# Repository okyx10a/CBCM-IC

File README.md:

# CBCM-IC Testing Platform
**Full-stack mixed-signal test fixture for Charge-Based Capacitance Measurement ICs**  
Designed, fabricated, and validated at York University (2018–2019)

*4-layer mixed-signal test board with separated analog/digital ground planes*

## Directory Structure
├── Hardware/                       → Altium project  
├── Software/                       → Arduino code + PyQt GUI  
├── Photos/                         → Assembly  
├── Test results/                   → Raw data and measurement data  
├── CBCM project summery.docx       → Test fixture construction explanation  
├── Tools chain setup.txt           → Note for succeeding developer  
└── README.md

## Key Features
- 4-layer KiCad design with proper analog/digital ground splitting
- SAM3X8E ARM Cortex-M3 (Arduino Due core) for real-time pattern generation and data acquisition
- Interfaces: SPI (20 MHz), UART
- SMT soldering down to 0603 passives and QFN packages (hand-soldered prototype)
- Automated measurement and data logging via Python + PyQt GUI

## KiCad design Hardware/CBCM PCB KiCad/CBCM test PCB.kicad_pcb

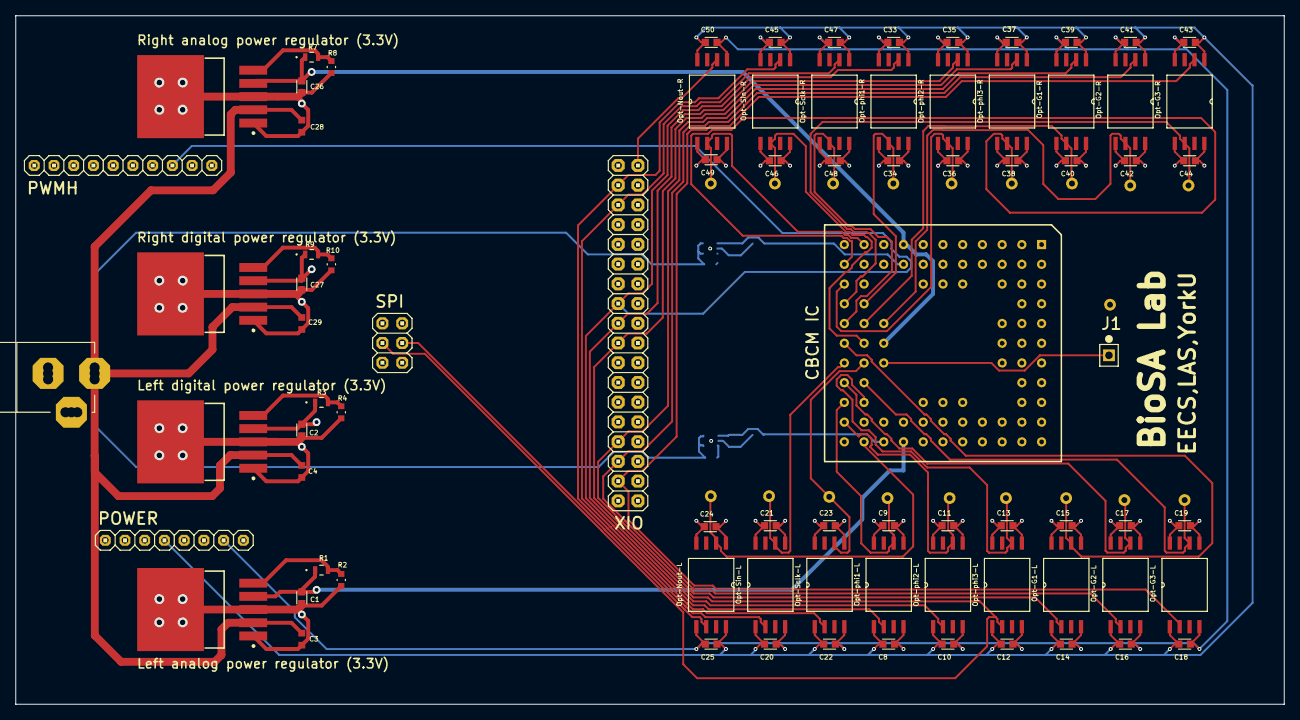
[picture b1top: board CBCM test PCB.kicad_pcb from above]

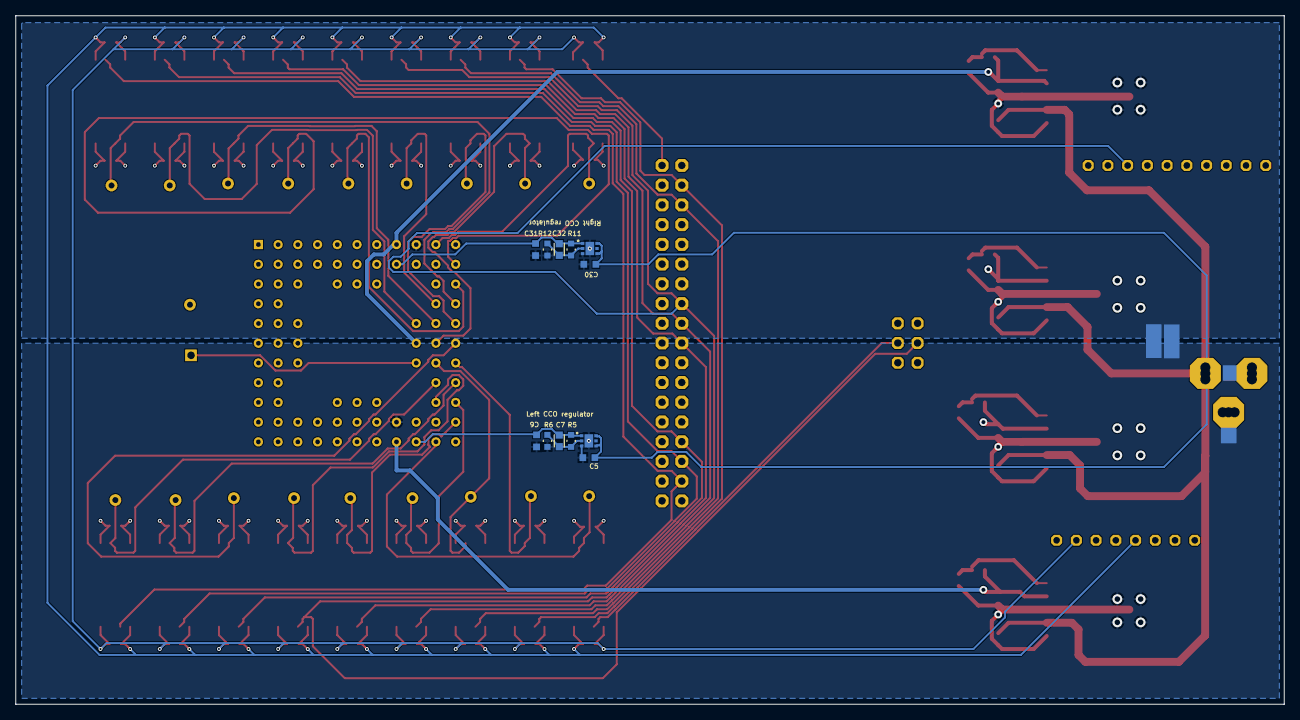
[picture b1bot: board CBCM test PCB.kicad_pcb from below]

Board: 4 copper layers, 163.3 x 88.6 mm, 99 parts (22 on the bottom side), 49 nets.

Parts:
C1, C2, C7, C8, C9, C10, C11, C12, C13, C14, C15, C16, C17, C18, C19, C20, C21, C22, C23, C24, C25, C26, C27, C32, C33, C34, C35, C36, C37, C38, C39, C40, C41, C42, C43, C44, C45, C46, C47, C48, C49, C50: C; CAPC1608X9N
C3, C4, C5, C6, C28, C29, C30, C31: C; CAP_GRM_188
CBCM IC: CBCM IC; PGA85x11
J1: 87224-1
Left CCO regulator: NCP705MTADJTCG; WDFN6
Left analog power regulator (3.3V): TPS75901KTTR; TO-263-5
Left digital power regulator (3.3V): TPS75901KTTR; TO-263-5
Opt-G1-L, Opt-G1-R, Opt-G2-L, Opt-G2-R, Opt-G3-L, Opt-G3-R: ADUM210N1BRIZ; SOIC127P1150X330-8N
Opt-Nout-L: ADUM210N1BRIZ; SOIC127P1150X330-8N
Opt-Nout-R: ADUM210N1BRIZ; SOIC127P1150X330-8N
Opt-Sclk-L: ADUM210N1BRIZ; SOIC127P1150X330-8N
Opt-Sclk-R: ADUM210N1BRIZ; SOIC127P1150X330-8N
Opt-Sin-L: ADUM210N1BRIZ; SOIC127P1150X330-8N
Opt-Sin-R: ADUM210N1BRIZ; SOIC127P1150X330-8N
Opt-phi1-L, Opt-phi1-R, Opt-phi2-L, Opt-phi2-R, Opt-phi3-L, Opt-phi3-R: ADUM210N1BRIZ; SOIC127P1150X330-8N
POWER: 8x1F-H8.5; 1X08
PWMH: 10x1F-H8.5; 1X10
R1, R3, R7, R9: R; RES_0816
R2, R4, R5, R6, R8, R10, R11, R12: R; RC0603N
Right CCO regulator: NCP705MTADJTCG; WDFN6
Right analog power regulator (3.3V): TPS75901KTTR; TO-263-5
Right digital power regulator (3.3V): TPS75901KTTR; TO-263-5
SPI: 3x2M; 2X03
X2: *; POWERSUPPLY_DC-21MM
XIO: 18x2F-H8.5; 2X18
tie1, tie2, tie3, tie4, tie5, tie6: Net Tie; net_tie

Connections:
+5: C3.2, C4.2, C5.2, C28.2, C29.2, C30.2, Left CCO regulator.4, Left CCO regulator.6, Left analog power regulator (3.3V).2, Left digital power regulator (3.3V).2, Right CCO regulator.4, Right CCO regulator.6, Right analog power regulator (3.3V).2, Right digital power regulator (3.3V).2, X2.2, X2.8, X2.9
D_GND: C2.1, C4.1, C9.2, C11.2, C13.2, C15.2, C17.2, C19.2, C21.2, C23.2, C24.2, C27.1, C29.1, C34.2, C36.2, C38.2, C40.2, C42.2, C44.2, C46.2, C48.2, C49.2, CBCM IC.K10, Left digital power regulator (3.3V).1, Left digital power regulator (3.3V).3, Left digital power regulator (3.3V).6, Opt-G1-L.5, Opt-G1-R.5, Opt-G2-L.5, Opt-G2-R.5, Opt-G3-L.5, Opt-G3-R.5, Opt-Nout-L.4, Opt-Nout-R.4, Opt-Sclk-L.5, Opt-Sclk-R.5, Opt-Sin-L.5, Opt-Sin-R.5, Opt-phi1-L.5, Opt-phi1-R.5, Opt-phi2-L.5, Opt-phi2-R.5, Opt-phi3-L.5, Opt-phi3-R.5, R4.2, R10.2, Right digital power regulator (3.3V).1, Right digital power regulator (3.3V).3, Right digital power regulator (3.3V).6, tie3.0, tie6.0
G1: Opt-G1-L.2, Opt-G1-R.2, XIO.29
G1-L: CBCM IC.L6, Opt-G1-L.6
G1-R: CBCM IC.K5, Opt-G1-R.6
G2: Opt-G2-L.2, Opt-G2-R.2, XIO.31
G2-L: CBCM IC.L8, Opt-G2-L.6
G2-R: CBCM IC.J5, Opt-G2-R.6
G3: Opt-G3-L.2, Opt-G3-R.2, XIO.33
G3-L: CBCM IC.K8, Opt-G3-L.6
G3-R: CBCM IC.L4, Opt-G3-R.6
LA_3.3: C1.2, CBCM IC.H11, Left analog power regulator (3.3V).4, R1.1
LA_GND: C1.1, C3.1, C5.1, C6.1, CBCM IC.H10, Left CCO regulator.3, Left CCO regulator.GND, Left analog power regulator (3.3V).1, Left analog power regulator (3.3V).3, Left analog power regulator (3.3V).6, R2.2, R6.2, tie1.0, tie2.1, tie4.1, tie5.0
LCCO_1.85V: C6.2, C7.1, CBCM IC.J11, Left CCO regulator.1, R5.1
LD_3.3: C2.2, C9.1, C11.1, C13.1, C15.1, C17.1, C19.1, C21.1, C23.1, C24.1, CBCM IC.J10, Left digital power regulator (3.3V).4, Opt-G1-L.8, Opt-G2-L.8, Opt-G3-L.8, Opt-Nout-L.1, Opt-Sclk-L.8, Opt-Sin-L.8, Opt-phi1-L.8, Opt-phi2-L.8, Opt-phi3-L.8, R3.1
NOUT: Opt-Nout-L.6, SPI.4
NOUT-L: CBCM IC.K11, Opt-Nout-L.2
NOUT-R: CBCM IC.K1, Opt-Nout-R.2
NOUT_TEST: Opt-Nout-R.6, XIO.2
NetC7_2: C7.2, Left CCO regulator.2, R5.2, R6.1
NetC32_2: C32.2, R11.2, R12.1, Right CCO regulator.2
NetCBCM IC_33: CBCM IC.J7, J1.1
NetLeft analog power regulator (3.3V)_5: Left analog power regulator (3.3V).5, R1.2, R2.1
NetLeft digital power regulator (3.3V)_5: Left digital power regulator (3.3V).5, R3.2, R4.1
NetR7_2: R7.2, R8.1, Right analog power regulator (3.3V).5
NetR9_2: R9.2, R10.1, Right digital power regulator (3.3V).5
Nettie1_1: X2.1, X2.4, X2.5, tie1.1, tie3.1
Nettie4_0: X2.3, X2.6, X2.7, tie4.0, tie6.1
PHI1: Opt-phi1-L.2, Opt-phi1-R.2, PWMH.3, XIO.15
PHI1-L: CBCM IC.L9, Opt-phi1-L.6
PHI1-R: CBCM IC.K4, Opt-phi1-R.6
PHI2: Opt-phi2-L.2, Opt-phi2-R.2, XIO.17
PHI2-L: CBCM IC.L10, Opt-phi2-L.6
PHI2-R: CBCM IC.L3, Opt-phi2-R.6
PHI3: Opt-phi3-L.2, Opt-phi3-R.2, SPI.3, XIO.19
PHI3-L: CBCM IC.K9, Opt-phi3-L.6
PHI3-R: CBCM IC.L2, Opt-phi3-R.6
RA_3.3: C26.2, CBCM IC.H1, CBCM IC.J6, R7.1, Right analog power regulator (3.3V).4
RA_GND: C26.1, C28.1, C30.1, C31.1, CBCM IC.J1, CBCM IC.L1, R8.2, R12.2, Right CCO regulator.3, Right CCO regulator.GND, Right analog power regulator (3.3V).1, Right analog power regulator (3.3V).3, Right analog power regulator (3.3V).6, tie2.0, tie5.1
RCCO_1.85V: C31.2, C32.1, CBCM IC.H2, R11.1, Right CCO regulator.1
RD_3.3: C27.2, C34.1, C36.1, C38.1, C40.1, C42.1, C44.1, C46.1, C48.1, C49.1, CBCM IC.J2, Opt-G1-R.8, Opt-G2-R.8, Opt-G3-R.8, Opt-Nout-R.1, Opt-Sclk-R.8, Opt-Sin-R.8, Opt-phi1-R.8, Opt-phi2-R.8, Opt-phi3-R.8, R9.1, Right digital power regulator (3.3V).4
SCLK: Opt-Sclk-L.2, Opt-Sclk-R.2, XIO.5
SCLK-L: CBCM IC.K7, Opt-Sclk-L.6
SCLK-R: CBCM IC.L5, Opt-Sclk-R.6
SIN: Opt-Sin-L.2, Opt-Sin-R.2, XIO.3
SIN-L: CBCM IC.L7, Opt-Sin-L.6
SIN-R: CBCM IC.K6, Opt-Sin-R.6
UC_3.3: C8.1, C10.1, C12.1, C14.1, C16.1, C18.1, C20.1, C22.1, C25.1, C33.1, C35.1, C37.1, C39.1, C41.1, C43.1, C45.1, C47.1, C50.1, Opt-G1-L.1, Opt-G1-R.1, Opt-G2-L.1, Opt-G2-R.1, Opt-G3-L.1, Opt-G3-R.1, Opt-Nout-L.8, Opt-Nout-R.8, Opt-Sclk-L.1, Opt-Sclk-R.1, Opt-Sin-L.1, Opt-Sin-R.1, Opt-phi1-L.1, Opt-phi1-R.1, Opt-phi2-L.1, Opt-phi2-R.1, Opt-phi3-L.1, Opt-phi3-R.1, POWER.4
UC_GND: C8.2, C10.2, C12.2, C14.2, C16.2, C18.2, C20.2, C22.2, C25.2, C33.2, C35.2, C37.2, C39.2, C41.2, C43.2, C45.2, C47.2, C50.2, Opt-G1-L.4, Opt-G1-R.4, Opt-G2-L.4, Opt-G2-R.4, Opt-G3-L.4, Opt-G3-R.4, Opt-Nout-L.5, Opt-Nout-R.5, Opt-Sclk-L.4, Opt-Sclk-R.4, Opt-Sin-L.4, Opt-Sin-R.4, Opt-phi1-L.4, Opt-phi1-R.4, Opt-phi2-L.4, Opt-phi2-R.4, Opt-phi3-L.4, Opt-phi3-R.4, POWER.6, POWER.7, SPI.6, XIO.35, XIO.36

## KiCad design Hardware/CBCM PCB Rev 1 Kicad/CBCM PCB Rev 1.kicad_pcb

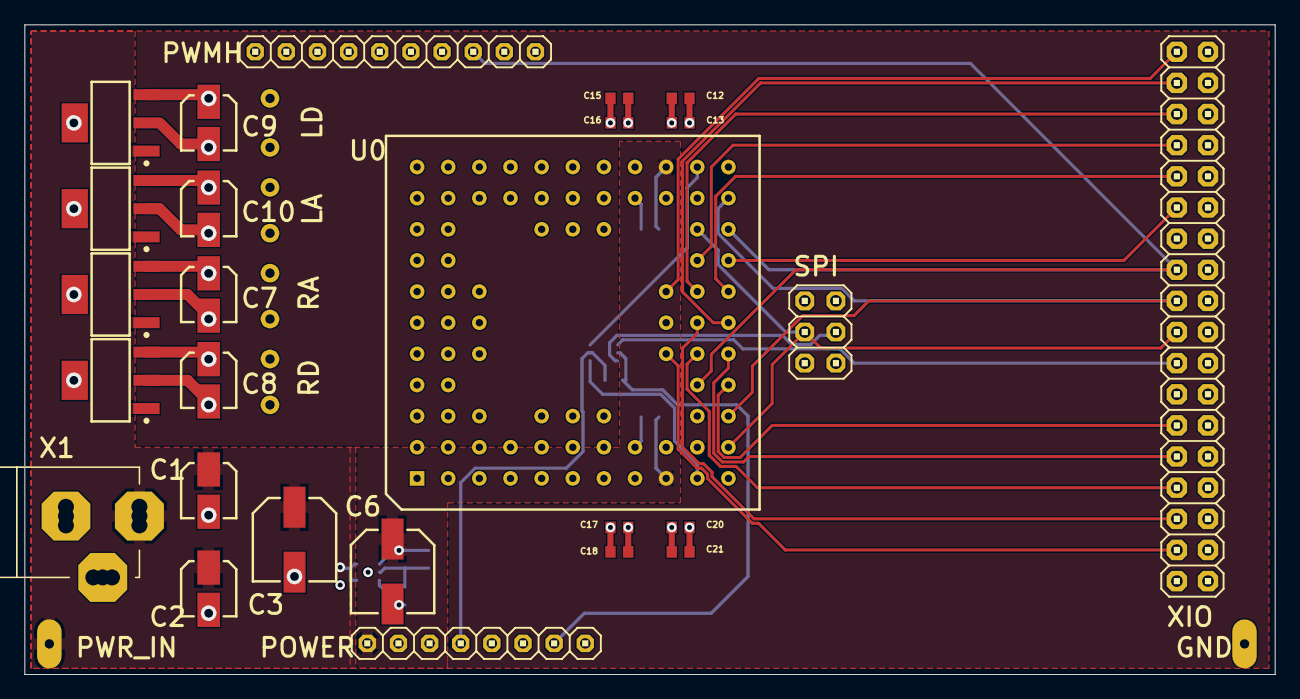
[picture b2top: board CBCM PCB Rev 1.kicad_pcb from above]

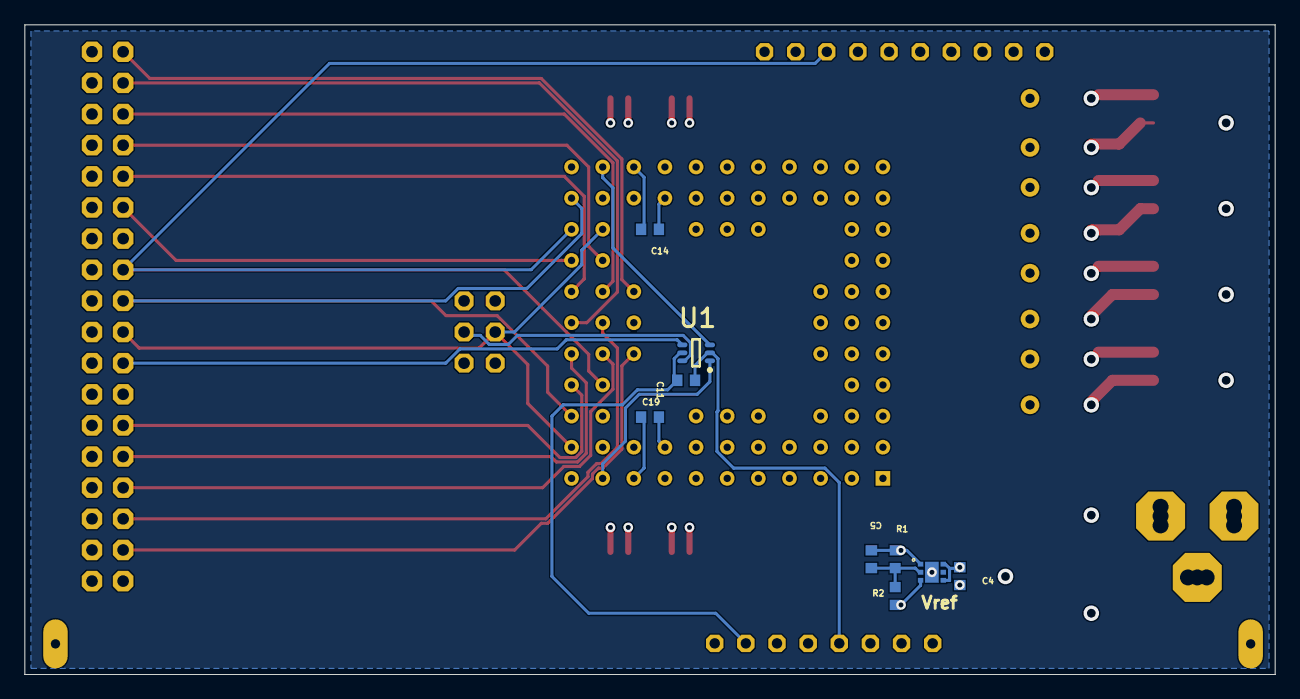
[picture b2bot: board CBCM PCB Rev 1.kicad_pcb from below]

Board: 4 copper layers, 102.0 x 53.0 mm, 35 parts (9 on the bottom side), 27 nets.

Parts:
C1, C7, C8, C9, C10: 10uF; CAPAE4643X55M
C2: 47uF; CAPAE4643X55M
C3, C6: 100uF; CAPAE7066X77M
C4, C13, C14, C16, C17, C19, C20: 1uF; CAPC1608X09N
C5: 10nF; CAPC1608X09N
C11, C12, C15, C18, C21: 0.1uF; CAPC1608X09N
LA: UA78M33QDCYRQ1; SOT230P700X180-4N
LD: UA78M33QDCYRQ1; SOT230P700X180-4N
POWER: 8x1F-H8.5; 1X08
PWMH: 10x1F-H8.5; 1X10
R1: 130k; RESC1608X09N
R2: 98.8k; RESC1608X09N
RA: UA78M33QDCYRQ1; SOT230P700X180-4N
RD: UA78M33QDCYRQ1; SOT230P700X180-4N
SPI: 3x2M; 2X03
U0: CBCM IC; PGA85x11
U1: TMUX1247; TSOP65P210X110-6N
Vref: NCP705MTADJTCG; WDFN6
X1: POWERSUPPLY_DC21MMX; POWERSUPPLY_DC-21MM
XIO: 18x2F-H8.5; 2X18

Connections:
COMMON_GND: C1.2, C2.2, C3.2, C4.2, C6.2, C7.2, C8.2, C9.2, C10.2, C11.1, C12.2, C13.2, C14.1, C15.2, C16.2, C17.1, C18.1, C19.2, C20.1, C21.1, LA.2, LA.4, LD.2, LD.4, POWER.6, POWER.7, R2.1, RA.2, RA.4, RD.2, RD.4, SPI.6, U0.H2, U0.H10, U0.K10, U0.L1, U1.5, Vref.3, Vref.GND, X1.1, X1.3, X1.4, X1.5, X1.6, X1.7, XIO.35, XIO.36
G1-L: U0.L6, XIO.3
G1-R: U0.K5, XIO.29
G2-L: U0.L8, XIO.11
G2-R: U0.J5, XIO.33
G3-L: U0.K8, XIO.7
G3-R: U0.L4, XIO.25
LAVDD: C10.1, C15.1, C16.1, LA.3, U0.H11
LDVDD: C9.1, C12.1, C13.1, LD.3, U0.J10
LNout: U0.K11, U1.3
NetC1_1: C1.1, C2.1, C3.1, C4.1, LA.1, LD.1, RA.1, RD.1, Vref.4, Vref.6, X1.2, X1.8, X1.9
NetC5_1: C5.1, R1.1, R2.2, Vref.2
Nout: SPI.4, U1.6
RAVDD: C7.1, C17.2, C18.2, RA.3, U0.H1, U0.J6
RDVDD: C8.1, C20.2, C21.2, RD.3, U0.J2
RNout: U0.K1, U1.1
SEL: U1.4, XIO.21
Sclk-L: U0.K7, XIO.5
Sclk-R: U0.L5, XIO.27
Sin-L: U0.L7, XIO.9
Sin-R: U0.K6, XIO.31
Test_Pin: U0.J7, XIO.1
Vref: C5.2, C6.1, C14.2, C19.1, POWER.1, R1.2, U0.J1, U0.J11, Vref.1
phi1: PWMH.3, U0.K4, U0.L9, XIO.15
phi2: U0.L3, U0.L10, XIO.17
phi3: SPI.3, U0.K9, U0.L2, XIO.19
uC_3V3: C11.2, POWER.4, U1.2

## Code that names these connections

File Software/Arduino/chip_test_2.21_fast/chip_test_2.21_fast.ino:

short result = 0;
int N_sample = 1000;

void setup() {
  Serial.begin(115200);
  
  // put your setup code here, to run once:
  REG_PMC_PCER1 |= PMC_PCER1_PID36;// Power up PWM clock
  REG_PWM_WPCR = PWM_WPCR_WPCMD(0);//Unlock user interface for PWM
  REG_PWM_CLK = PWM_CLK_PREA(0)|PWM_CLK_DIVA(21); //config the PWM clock generator: clock A, 84/21 = 4MHz
  REG_PWM_SCM = PWM_SCM_SYNC0|PWM_SCM_SYNC1;//Synchronize phi1 and phi2 for they have the same frequency
   
  //config phi1, Output pin PC2, Digital pin 34
  REG_PIOC_ABSR |= PIO_ABSR_P2; // Transfer Pin control from PIO to PWM
  REG_PIOC_PDR |= PIO_PDR_P2;   // Set PWM pin to an output
  REG_PWM_CMR0 = PWM_CMR_CPRE_CLKA; //mode congiration for channel 0: clock A, letft aligned, waveform start at high
  REG_PWM_CPRD0 = PWM_CPRD_CPRD(60);//config period for pwm 60/(4MHz)
  REG_PWM_CDTY0 = PWM_CDTY_CDTY(16);// 80/3% duty cycle
  REG_PWM_ENA = PWM_ENA_CHID0;// enable PWM channel0
  
  //config phi2, Output pin PC4, Digital pin 36
  REG_PIOC_ABSR |= PIO_ABSR_P4; // Transfer Pin control from PIO to PWM
  REG_PIOC_PDR |= PIO_PDR_P4;   // Set PWM pin to an output
  REG_PWM_CMR1 = PWM_CMR_CPRE_CLKA|PWM_CMR_DTE; //mode congiration for channel 0: clock A, letft aligned, waveform start at high
  REG_PWM_CPRD1 = PWM_CPRD_CPRD(60);//config period for pwm 60/(4MHz)
  REG_PWM_DT1 = PWM_DT_DTL(4); //create the 1us(delay)
  REG_PWM_CDTY1 = PWM_CDTY_CDTY(12);// 80/3% duty cycle
  REG_PWM_ENA = PWM_ENA_CHID1;// enable PWM channel1
  
  //config phi3, Output pin PC6, Digital pin 38
  REG_PIOC_ABSR |= PIO_ABSR_P6; // Transfer Pin control from PIO to PWM
  REG_PIOC_PDR |= PIO_PDR_P6;   // Set PWM pin to an output
  REG_PWM_CMR2 = PWM_CMR_CPRE_CLKA;//mode congiration for channel 0: clock A, letft aligned, waveform start at low
  REG_PWM_CPRD2 = PWM_CPRD_CPRD(2);//config period for pwm 2/(4MHz)
  REG_PWM_CDTY2 = PWM_CDTY_CDTY(1);//50% duty cycle
  REG_PWM_ENA = PWM_ENA_CHID2;// enable PWM channel2
  
  //SPI serial recieve 
  REG_PMC_PCER0 |= PMC_PCER0_PID24;// Power up SPI clock
  REG_SPI0_WPMR = 0<<SPI_WPMR_WPEN;//Unlock user interface for SPI
  
  //Instance SPI0, MISO: PA25, (MISO), MOSI: PA26, (MOSI), SCLK: PA27, (SCLK), NSS: PA28, Digital pin 10 
  REG_PIOA_ABSR |= PIO_ABSR_P25; // Transfer Pin control from PIO to SPI
  REG_PIOA_PDR |= PIO_PDR_P25;   // Set MISO pin to an output

  REG_PIOA_ABSR |= PIO_ABSR_P26; // Transfer Pin control from PIO to SPI
  REG_PIOA_PDR |= 0<<PIO_PDR_P26;   // Set MOSI pin to an input

  REG_PIOA_ABSR |= PIO_ABSR_P27; // Transfer Pin control from PIO to SPI
  REG_PIOA_PDR |= 0<<PIO_PDR_P27;   // Set SCLK pin to an input

  REG_PIOA_ABSR |= PIO_ABSR_P28; // Transfer Pin control from PIO to SPI
  REG_PIOA_PDR |= 0<<PIO_PDR_P28;   // Set NSS pin to an input

  //REG_ISER0 = 1<<24; //Enable interrupt controller
  REG_SPI0_CR = 1; // Enable SPI
  REG_SPI0_MR = 0; // Slave mode  
  REG_SPI0_IER = 1<<SPI_IER_RDRF|1<<SPI_IER_OVRES|1<<SPI_IER_NSSR; //Enable interrupts
  SPI0->SPI_CSR[0] = SPI_CSR_BITS_12_BIT; // Capture on falling edge and transfer 12 bits.

  pinMode(22,OUTPUT);// Sin
  pinMode(24,OUTPUT);// Sclk
  pinMode(48,OUTPUT);//G1
  pinMode(50,OUTPUT);//G2
  pinMode(52,OUTPUT);//G3
  digitalWrite(48,HIGH);
  digitalWrite(50,HIGH);
  digitalWrite(52,HIGH);
  delay(100);
  digitalWrite(22, LOW);
  digitalWrite(24, LOW);  
  //inputSig("00010011"); 
  digitalWrite(22, LOW);
  digitalWrite(24, LOW); 
  delay(10);
}

void inputSig(char testSeq[])
{
  //turn off the phi clock pulses
  REG_PWM_DIS = PWM_DIS_CHID0;
  REG_PWM_DIS = PWM_DIS_CHID1;
  REG_PWM_DIS = PWM_DIS_CHID2;
  delayMicroseconds(1);
  //fully reset the input registers
  for(int i = 13; i>0 ;i--)
  {
     digitalWrite(22, LOW);
     digitalWrite(24, LOW);
     delay(1);      
     digitalWrite(24,HIGH);
     delay(1);
  }
  //apply input sequences
  for(int i = 0; i<7 ;i++)
  {
    if(testSeq[i] == '0')
    {
      digitalWrite(22, LOW);
      digitalWrite(24, LOW);
      delay(1);      
      digitalWrite(24,HIGH);
      delay(1);
    }  
    else if(testSeq[i] == '1')
    {
      digitalWrite(22, HIGH);
      digitalWrite(24, LOW);
      delay(1);      
      digitalWrite(24,HIGH);
      delay(1);
    }
  }
  delayMicroseconds(1);
  digitalWrite(22, LOW);
  digitalWrite(24, LOW);
  //turn the phi pulses back on
  REG_PWM_ENA = PWM_ENA_CHID0;
  REG_PWM_ENA = PWM_ENA_CHID1;
  REG_PWM_CMR2 = 0;
  REG_PWM_CMR2 = PWM_CMR_CPRE_CLKA;
  REG_PWM_CMR2 &= ~PWM_CMR_CPOL;
  REG_PWM_ENA = PWM_ENA_CHID2;
}

void loop() {
  //inputSig("11101010"); 
  char calin_i[7];
  //Serial.println(1);
  if(Serial.available()>0)
  {
    //Serial.println(2);
    char temp = Serial.read();
    switch (temp)
    {
      case 'S':   
        for(int i = 0; i<4; )
        {
          if(Serial.available() > 0) 
          {      
            calin_i[i] = Serial.read();
            i++;
          }
        }
        calin_i[4] = '\0';
        N_sample = atoi(calin_i);
        //Serial.println(calin_i); 
        Serial.println(N_sample); 
        break;
      case 'W':
        for(int i = 0; i<7; )
        {
          if(Serial.available() > 0) 
          {      
            calin_i[i] = Serial.read();
            i++;
          }
        }
        inputSig(calin_i);
        break;
      case 'G':
        for(int i = 0; i<3; )
        {
          if(Serial.available() > 0) 
          {      
            calin_i[i] = Serial.read();
            i++;
          }
          if(calin_i[i] == '1')
            digitalWrite(48+i,HIGH);
          else
            digitalWrite(48+i,LOW);
        }
        break;
      case 'R':
        unsigned char buf[N_sample*sizeof(short)];
        for(int i = 0;i<N_sample;)
        {
          if(REG_SPI0_SR&1)
          {
            result = REG_SPI0_RDR;  
            buf[2*i] = highByte(result);
            buf[2*i+1] = lowByte(result); 
            i++;
           }    
        } 
        delay(1);
        Serial.write(buf,N_sample*sizeof(short)); 
        Serial.flush();
        break;
       default:
        Serial.println('\0');
        break;       
    }
     
  }
  
}

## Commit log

2019-01-17 Initail commit on github
    Read out software is able to take 1000+ samples per calibration point
2019-01-22 Sample number change and hydro gel test results
    1) Added option to change the number of samples.
    2) Added testing result with hydro gels
2019-02-13 Generated python GUI code
    Task to be done:
    1) display debug message in the Qtext browser.
    2) implement all button handlers
    3) integrate graph window(optional)
2019-02-14 GUI working with minor bugs
    1) feed back on the sample change incorrect(actual number of sample written to the microcontroller is correct)
    2)need to implement automactic port closure on exit
    3)need to implement feed back of CCO resolution
    4) disable all buttons when port is occupied.
2019-02-18 GUI fully functional, chemical tests added
    potential improvements:
    add a new thread for calibraiton scan.
    add a welcome message and instructions in the text browser.
2019-02-21 02-20-2019 chemical test results
2019-04-04 real time data streaming (unfinished)
    graph does not auto update:
    1) might because a lack of auto updating time axis
    2) the loop is not running
    program cashs after clicking stop button
2019-04-12 Real time monitoring of a single calibration value
    Things are done:
    Real time monitoring of a single calibration value functional
    Things to be done:
    1) Keep the plot window paused on hitting the stop button
    2) Add spectrum analysis, multiple continuous calibration value scan
    3) Add default value for parameter settings
2019-04-18 Spectrum analysis done
    To be done:
    1) Keep the plot window paused on hitting the stop button
    2) Add default value for parameter settings
    3) Add welcome message and usage instructions in the text area on start up
2019-04-26 Added a short summery
2019-05-10 Fixing the average value bug
2019-05-11 ignore older version of GUI
2019-06-13 Fix the bug that input dosen't include the mode swap bit
    Fix the bug that input dosen't include the mode swap bit
    Now input has 8 bits, the additional bit swaps the chip between calibration mode and sensing mode.
2019-06-21 Fix a bug where arduino is not returning input values
2019-07-05 Final test version(messy need reorganize)
    1) The final version of both arduino and GUI code are in the -copy folder
    2) Final test result proving the spikes on the right side are a result of oscillator behavior
2019-09-05 Started designs on CBCMmin PCB
2019-09-06 05-09-2019
2019-09-20 19-09-2019
    minature PCB in progress
2019-11-30 11-29-2019
2020-03-06 UI ver 2.26
2020-03-10 03-09-2020
2020-03-27 2.26GUI
2020-07-28 CBCM PCB Rev 1
2020-07-31 CBCM Rev1 reviewed
2025-12-09 Add photo and Kicad version of the design
2025-12-09 update Readme (私とココの将来のために)
2025-12-10 Add photos of the project.
